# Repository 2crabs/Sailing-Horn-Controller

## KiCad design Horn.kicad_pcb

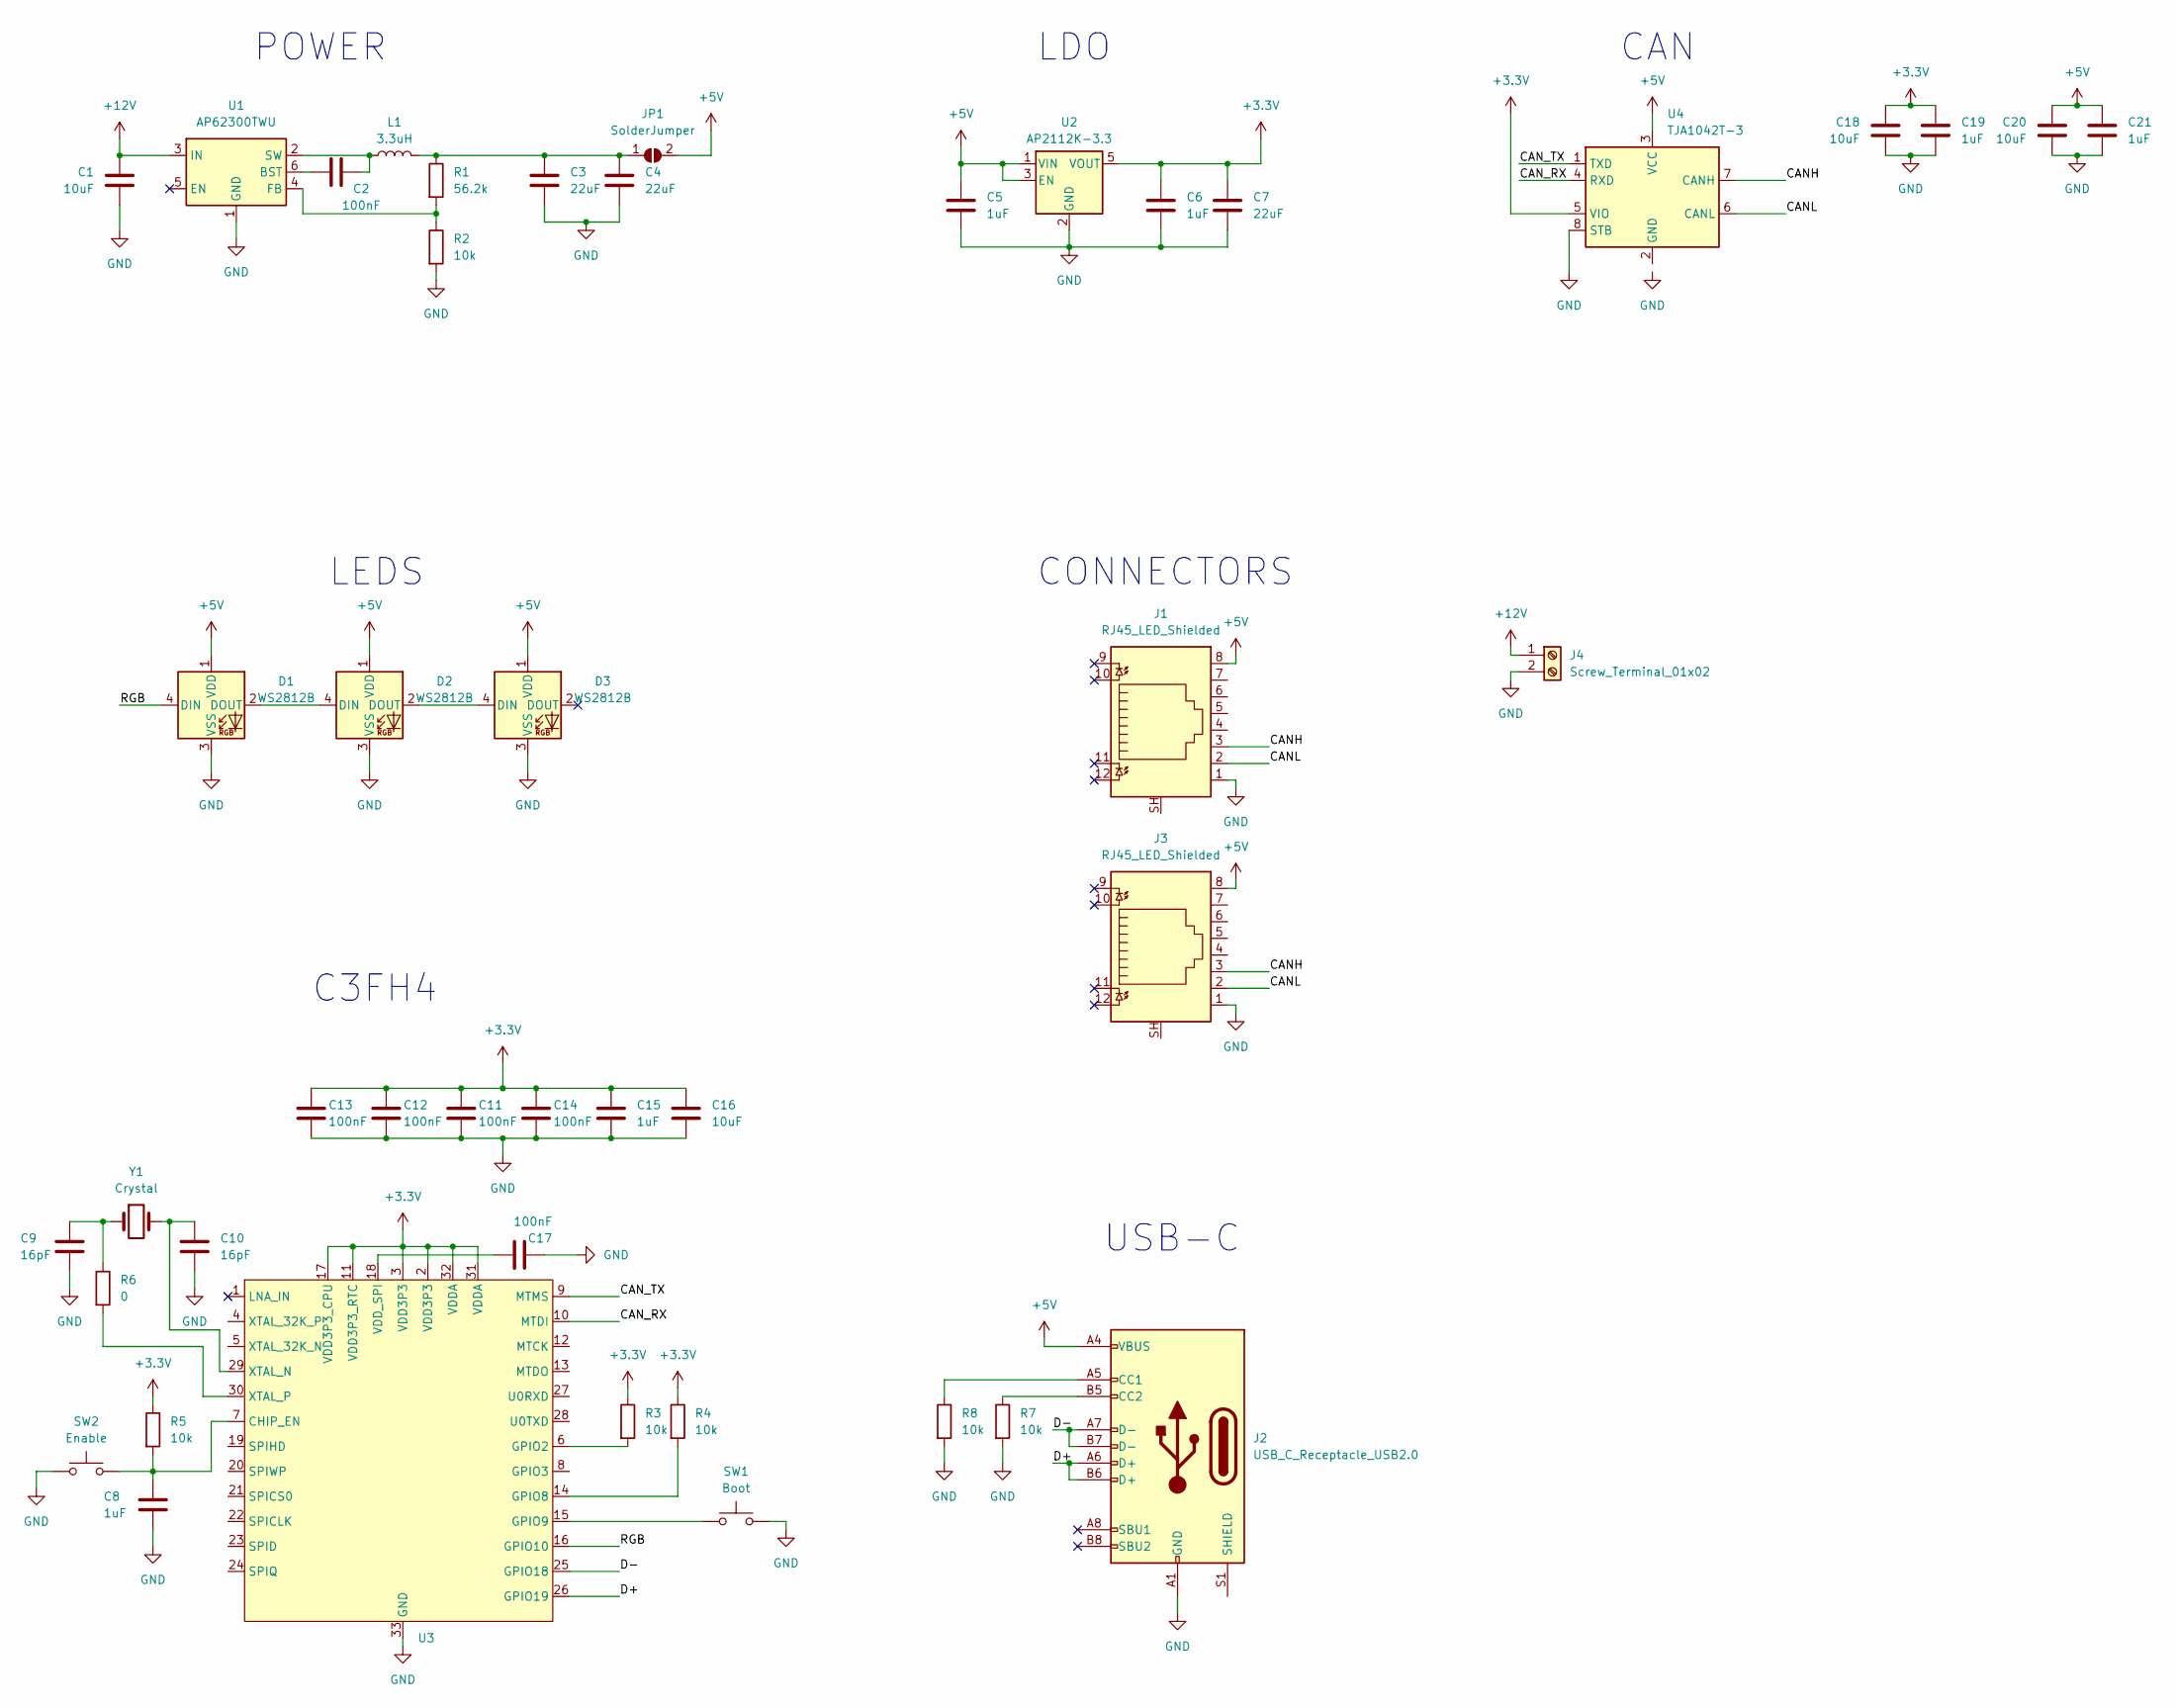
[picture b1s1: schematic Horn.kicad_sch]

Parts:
C1: 10uF; C_0805_2012Metric
C2, C11, C12, C13, C14, C17: 100nF; C_0603_1608Metric
C3, C4, C7: 22uF; C_0805_2012Metric
C5, C6, C8, C15, C19, C21: 1uF; C_0603_1608Metric
C9, C10: 16pF; C_0603_1608Metric
C16, C18, C20: 10uF; C_0603_1608Metric
D1, D2, D3: WS2812B; LED_WS2812B-2020_PLCC4_2.0x2.0mm
J1, J3: RJ45_LED_Shielded; RJ45_Connfly_DS1128-09-S8xx-S_Horizontal
J2: USB_C_Receptacle_USB2.0; USB_C_Receptacle_G-Switch_GT-USB-7010ASV
J4: Screw_Terminal_01x02; TerminalBlock_MetzConnect_Type011_RT05502HBWC_1x02_P5.00mm_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
JP1: SolderJumper; SolderJumper-2_P1.3mm_Open_RoundedPad1.0x1.5mm
L1: 3.3uH; L_Sunlord_SWPA4030S
R1: 56.2k; R_0603_1608Metric
R2, R3, R4, R5, R7, R8: 10k; R_0603_1608Metric
R6: 0; R_0603_1608Metric
SW1: Boot; SW_SPST_Omron_B3FS-101xP
SW2: Enable; SW_SPST_Omron_B3FS-101xP
U1: AP62300TWU; TSOT-23-6
U2: AP2112K-3.3; SOT-23-5
U3: QFN-32-1EP_5x5mm_P0.5mm_EP3.3x3.3mm
U4: TJA1042T-3; SOIC-8_3.9x4.9mm_P1.27mm
Y1: Crystal; Crystal_SMD_MicroCrystal_CC5V-T1A-2Pin_4.1x1.5mm

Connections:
+3.3V: C6.1, C7.1, C11.1, C12.1, C13.1, C14.1, C15.1, C16.1, C18.1, C19.1, R3.1, R4.1, R5.1, U2.5 (VOUT), U3.2 (VDD3P3), U3.3 (VDD3P3), U3.11 (VDD3P3_RTC), U3.17 (VDD3P3_CPU), U3.31 (VDDA), U3.32 (VDDA), U4.5 (VIO)
+5V: C5.1, C20.1, C21.1, D1.1 (VDD), D2.1 (VDD), D3.1 (VDD), J1.8, J2.A4 (VBUS), J2.A9 (VBUS), J2.B4 (VBUS), J2.B9 (VBUS), J3.8, JP1.2 (B), U2.1 (VIN), U2.3 (EN), U4.3 (VCC)
+12V: C1.1, J4.1, U1.3 (IN)
/CANH: J1.3, J3.3, U4.7 (CANH)
/CANL: J1.2, J3.2, U4.6 (CANL)
/CAN_RX: U3.10 (MTDI), U4.4 (RXD)
/CAN_TX: U3.9 (MTMS), U4.1 (TXD)
/D+: J2.A6 (D+), J2.B6 (D+), U3.26 (GPIO19)
/D-: J2.A7 (D-), J2.B7 (D-), U3.25 (GPIO18)
/RGB: D1.4 (DIN), U3.16 (GPIO10)
GND: C1.2, C3.2, C4.2, C5.2, C6.2, C7.2, C8.2, C9.2, C10.2, C11.2, C12.2, C13.2, C14.2, C15.2, C16.2, C17.2, C18.2, C19.2, C20.2, C21.2, D1.3 (VSS), D2.3 (VSS), D3.3 (VSS), J1.1, J2.A1 (GND), J2.A12 (GND), J2.B1 (GND), J2.B12 (GND), J3.1, J4.2, R2.2, R7.2, R8.2, SW1.2, SW2.1, U1.1 (GND), U2.2 (GND), U3.33 (GND), U4.8 (STB)
unnamed: C9.1, R6.1, Y1.1
unnamed: D1.2 (DOUT), D2.4 (DIN)
unnamed: D2.2 (DOUT), D3.4 (DIN)
unnamed: J2.A5 (CC1), R8.1
unnamed: J2.B5 (CC2), R7.1
unnamed: C3.1, C4.1, JP1.1 (A), L1.2, R1.1
unnamed: C2.1, U1.6 (BST)
unnamed: R1.2, R2.1, U1.4 (FB)
unnamed: C2.2, L1.1, U1.2 (SW)
unnamed: C8.1, R5.2, SW2.2, U3.7 (CHIP_EN)
unnamed: R3.2, U3.6 (GPIO2)
unnamed: R4.2, U3.14 (GPIO8)
unnamed: SW1.1, U3.15 (GPIO9)
unnamed: C17.1, U3.18 (VDD_SPI)
unnamed: C10.1, U3.29 (XTAL_N), Y1.2
unnamed: R6.2, U3.30 (XTAL_P)

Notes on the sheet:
POWER
CONNECTORS
USB-C
CAN
LDO
LEDS
C3FH4

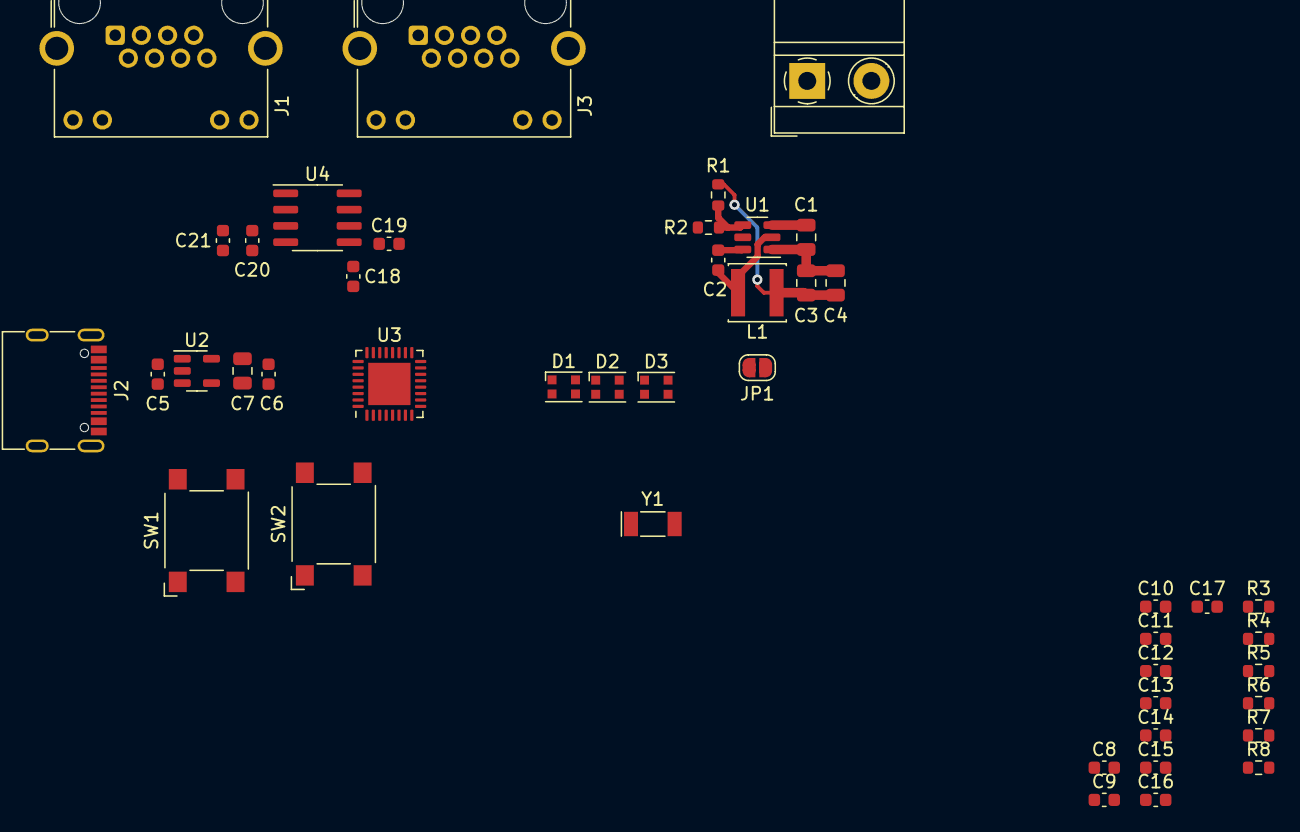
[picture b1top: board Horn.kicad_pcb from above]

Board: 2 copper layers, 45 parts (0 on the bottom side), 27 nets.

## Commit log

2023-12-20 Create Project
2023-12-20 Add dc-dc converter
2023-12-20 Added LDO
2023-12-20 Added esp32c3
2023-12-22 Added microcontroller
2023-12-27 Added Transceiver
2023-12-30 Chose component sizes
2024-01-04 Started PCB
